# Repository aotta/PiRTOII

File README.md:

# PiRTO II
Intellivision flash multicart based on Pico clone

PiRTO II  is the new version of my PiRTO multicart DIY yourself based on cheap "purple" Raspberry Pi Pico clone.

(use "alternate_boot" version if your PiRTO doesn't start without resetting it and/or the console).

added v. 1.01: bug fixed (added test if more than 64 files in a folder)

added v. 1.02: bug fixed (fix for Coleco Rom from previous version)

added v. 1.03: bug fixed (issue in Chess after move #21)

added v. 1.04: bug fixed Missile Domination (added support for both RAM8 and RAM16) and added initialization fix used by gtortone for his "Minty" for better compatibility

added v. 1.05beta Arduino IDE version, new environment left more ram space and let games until 180kb run. Fixed Time Pilot. WARNING!!! THIS NEW VERSION USE A NEW FILE SYSTEM AND YOU NEED TO FORMAT THE PICO FLASH AND RE-UPLOAD ALL BIN+CFG FILES!!!!!

**WARNING!** "purple" Pico has not the same pinout of original Raspberry "green" ones, you MUST use the clone or you may damage your hardware.

**NOTE** FAT FS used for flash file management is quite simple, you can't use FILENAME LONGER THAN 32 BYTES INCLUDED SUFFIX!!!!! 
PLEASE RENAME YOUR BIN FILES OR THE GAMES WON'T START AT ALL!!! 

Kicad project and gerbers files for the pcb are in the PCB folder, you need only a diode and a push buttons for resetting the cart if needed or want restart. 
Add you pico clone, and flash the firmware ".uf2" in the Pico by connecting it while pressing button on Pico and drop it in the opened windows on PC.
After flashed with firmware, and every time you have to change your ROMS repository, you can simply connect the Pico to PC and drag&drop "BIN" and "CFG“ files  into.

More info on AtariAge forum: https://forums.atariage.com/

Even if the diode should protect your console, **DO NOT CONNECT PICO WHILE INSERTED IN A POWERED ON CONSOLE!**
You can use any schottky diode, i usually put 1n4148

## Credits
Thank to Robin Robin Edwards and his A8PicoCart (https://github.com/robinhedwards/A8PicoCart), i found very smart his way to manage the Flash RAM and the USB updates, so i admit i took large parte of his code for it!.

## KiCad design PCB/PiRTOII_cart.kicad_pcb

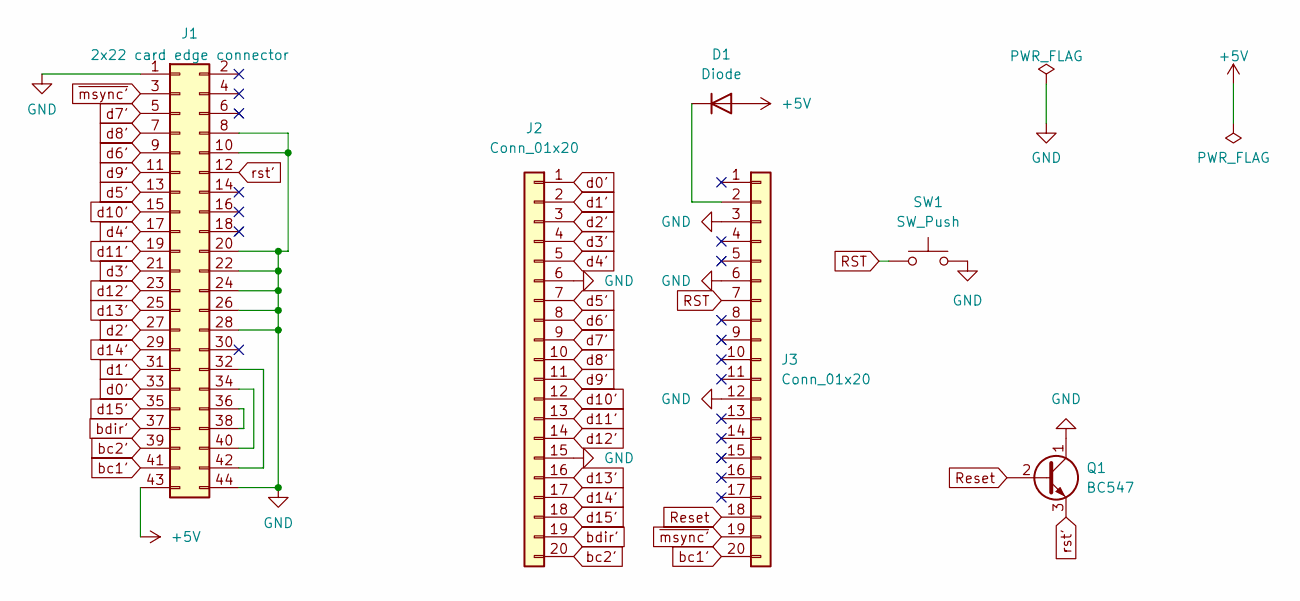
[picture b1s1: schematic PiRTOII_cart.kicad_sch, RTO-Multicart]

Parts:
D1: Diode; D_DO-35_SOD27_P7.62mm_Horizontal
J1: 2x22 card edge connector; edge mounted 44 pin card edge connector (2x22 pin)
J2, J3: Conn_01x20; PinSocket_1x20_P2.54mm_Vertical
Q1: BC547; TO-92_Inline
SW1: SW_Push; SW_Tactile_SPST_Angled_PTS645Vx83-2LFS

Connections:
+5V: D1.2 (A), J1.43
GND: J1.1, J1.8, J1.10, J1.20, J1.22, J1.24, J1.26, J1.28, J1.44, J2.6, J2.15, J3.3, J3.6, J3.12, Q1.1 (C), SW1.2
unnamed: D1.1 (K), J3.2
unnamed: J1.32, J1.42
unnamed: J1.34, J1.40
unnamed: J1.36, J1.38
RST: J3.7, SW1.1
Reset: J3.18, Q1.2 (B)
bc1': J1.41, J3.20
bc2': J1.39, J2.20
bdir': J1.37, J2.19
d0': J1.33, J2.1
d1': J1.31, J2.2
d2': J1.27, J2.3
d3': J1.21, J2.4
d4': J1.17, J2.5
d5': J1.13, J2.7
d6': J1.9, J2.8
d7': J1.5, J2.9
d8': J1.7, J2.10
d9': J1.11, J2.11
d10': J1.15, J2.12
d11': J1.19, J2.13
d12': J1.23, J2.14
d13': J1.25, J2.16
d14': J1.29, J2.17
d15': J1.35, J2.18
rst': J1.12, Q1.3 (E)
~msync': J1.3, J3.19

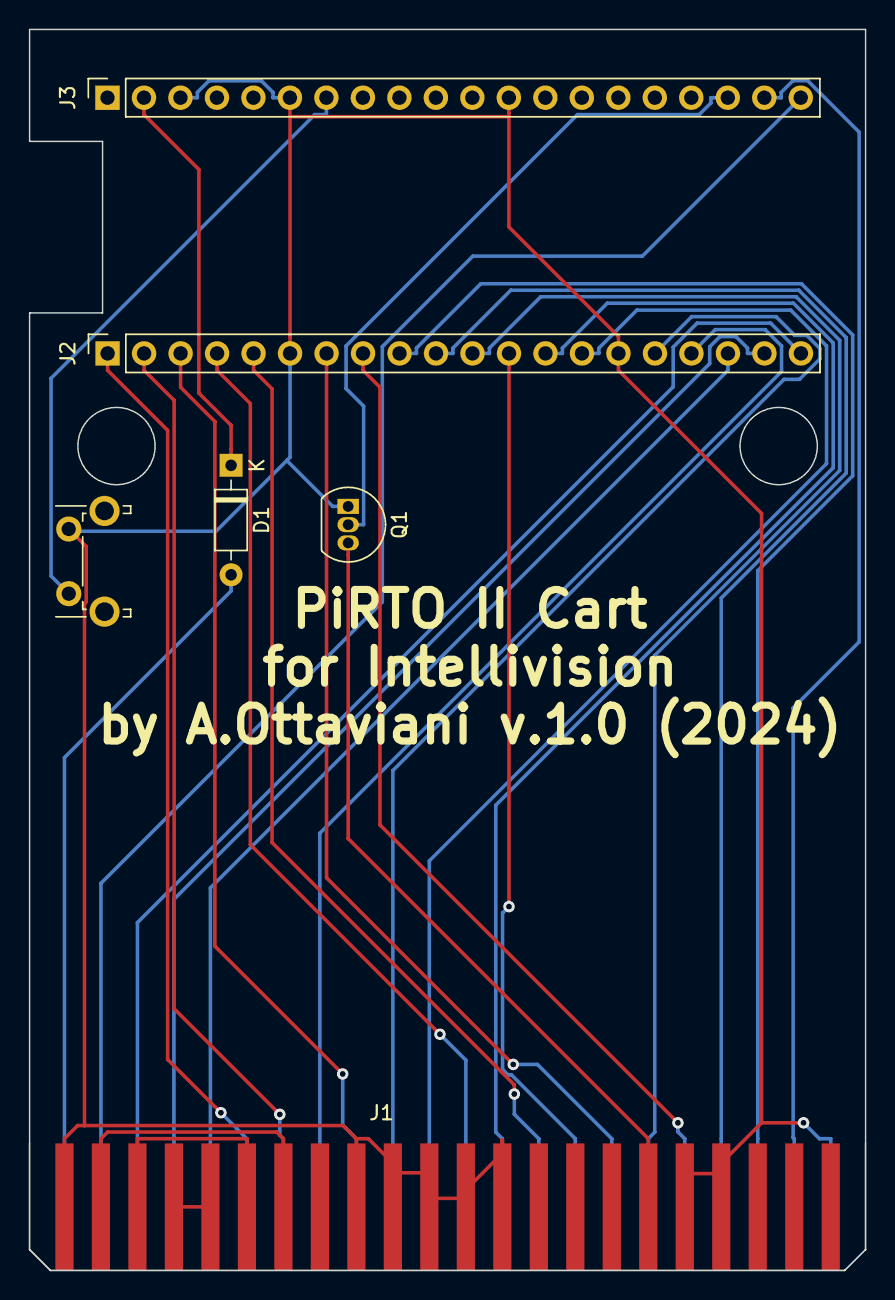
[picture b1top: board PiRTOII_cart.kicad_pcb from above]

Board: 2 copper layers, 58.2 x 86.4 mm, 6 parts (0 on the bottom side), 29 nets.

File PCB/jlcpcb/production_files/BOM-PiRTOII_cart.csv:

Comment,Designator,Footprint,LCSC
Conn_01x20,J2,PinSocket_1x20_P2.54mm_Vertical,
2x22 card edge connector,J1,edge mounted 44 pin card edge connector (2x22 pin),
SW_Push,SW1,SW_Tactile_SPST_Angled_PTS645Vx83-2LFS,
Conn_01x20,J3,PinSocket_1x20_P2.54mm_Vertical,
Diode ,D1,D_DO-35_SOD27_P7.62mm_Horizontal,
BC547,Q1,TO-92_Inline,

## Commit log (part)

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2024-08-07 Update inty_cart.c
    bug fixed in hacks check
2024-10-28 New improved shell version by Eskimo
2025-01-09 Add files via upload
    v. 1.01 bug fix (added test if more than 64 files in a folder)
2025-01-09 Update README.md
    v. 1.01 bug fixed (added test if more than 64 files in a folder)
2025-04-28 fixed bug in hacks section
2025-04-28 bug in hacks sectino fixed
2025-04-28 fixed error in Chess
2025-04-28 v. 1.03
2025-04-30 alternate boot fixed to v.1.03
2025-10-03 Update README.md
    V.1.04 bug fix Missile Domination
2025-10-03 Add files via upload
    V.1.04 bug fix Missile Domination
2025-10-03 V.1.04 bug fix Missile Domination
2025-10-12 Used initialization fix used by gtortone
    Used initialization fix used by gtortone in his "Minty" for better compatibility
2025-10-16 Add files via upload
    V.1.05beta - warning you need to reformat flash and reupload all games!
2025-10-16 Add files via upload
    Porting to Arduino IDE (since V.1.05) - need flash reformat!!!
2025-10-16 Update README.md
    Added v.1.05beta description
2025-10-16 Add files via upload
    further bugfixes
2025-10-16 Add files via upload
    bugfixes
2025-10-18 Add files via upload
    update to 1.05 beta 7
